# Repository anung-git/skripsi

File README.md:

# skripsi
skripsi pompa air iot

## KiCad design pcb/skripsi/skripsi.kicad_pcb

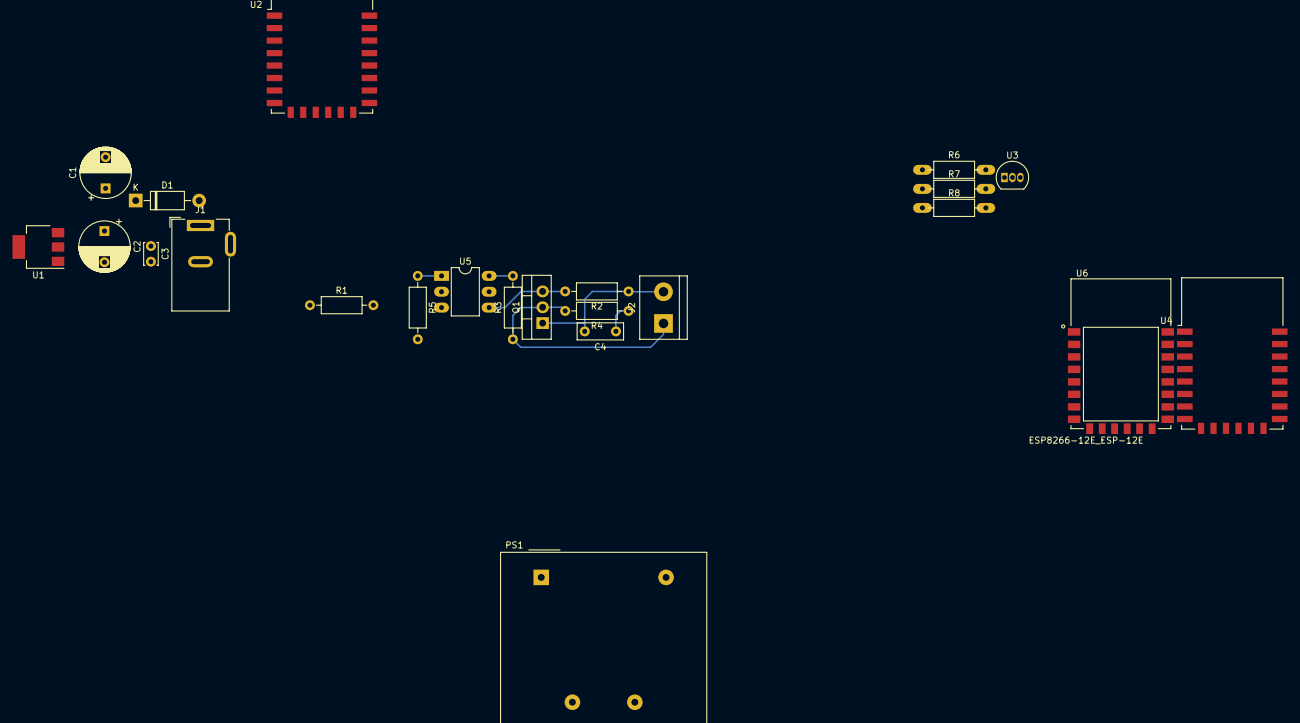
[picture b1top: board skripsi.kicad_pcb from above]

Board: 2 copper layers, 23 parts (0 on the bottom side), 14 nets.

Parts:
C1: 470uF/16v; CP_Radial_D8.0mm_P5.00mm
C2: 100uF/16v; CP_Radial_D8.0mm_P5.00mm
C3: 100nF; C_Disc_D3.4mm_W2.1mm_P2.50mm
C4: 10nF/1000v; C_Rect_L7.2mm_W2.5mm_P5.00mm_FKS2_FKP2_MKS2_MKP2
D1: 1n4002; D_DO-41_SOD81_P10.16mm_Horizontal
J1: Jack-DC; BarrelJack_Wuerth_6941xx301002
J2: motor; TerminalBlock_bornier-2_P5.08mm
PS1: HS-40003; Converter_ACDC_Hahn_HS-400xx_THT
Q1: BT136-500; TO-220-3_Vertical
R1, R7, R8: 10k; R_Axial_DIN0207_L6.3mm_D2.5mm_P10.16mm_Horizontal
R2: 330; R_Axial_DIN0207_L6.3mm_D2.5mm_P10.16mm_Horizontal
R3: 360; R_Axial_DIN0207_L6.3mm_D2.5mm_P10.16mm_Horizontal
R4: 39; R_Axial_DIN0207_L6.3mm_D2.5mm_P10.16mm_Horizontal
R5: 68; R_Axial_DIN0207_L6.3mm_D2.5mm_P10.16mm_Horizontal
R6: 4k7; R_Axial_DIN0207_L6.3mm_D2.5mm_P10.16mm_Horizontal
U1: AP1117-33; SOT-223-3_TabPin2
U2: ESP-12E
U3: DS18B20; TO-92_Inline
U4: ESP-12F; ESP-12E
U5: MOC3041M; DIP-6_W7.62mm_LongPads
U6: ESP8266-12E_ESP-12E; XCVR_ESP8266-12E%2fESP-12E

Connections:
+3V3: C2.1, C3.1, R1.1, R6.1, R7.1, U1.2, U2.8, U3.3
+5V: C1.1, D1.1, U1.3
GND: C1.2, C2.2, C3.2, J1.2, R8.2, U1.1, U2.15, U3.1, U5.2
unnamed: C4.1, R4.1
unnamed: C4.2, J2.2, Q1.1, R2.1
unnamed: D1.2, J1.1
unnamed: J2.1, Q1.2, R3.1, R4.2
unnamed: Q1.3, R2.2, U5.4
unnamed: R1.2, U2.1
unnamed: R3.2, U5.6
unnamed: R5.1, U5.1
unnamed: R7.2, U2.18
unnamed: R8.1, U2.16
temp: R6.2, U3.2

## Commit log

2020-08-02 laporan
2020-08-02 revisi
2020-08-05 tambah software
2020-08-06 FLOWCHART
2020-08-10 revisi daya pompa
2020-08-13 yudisium
2020-08-16 lampiran
2020-08-17 jurnal
